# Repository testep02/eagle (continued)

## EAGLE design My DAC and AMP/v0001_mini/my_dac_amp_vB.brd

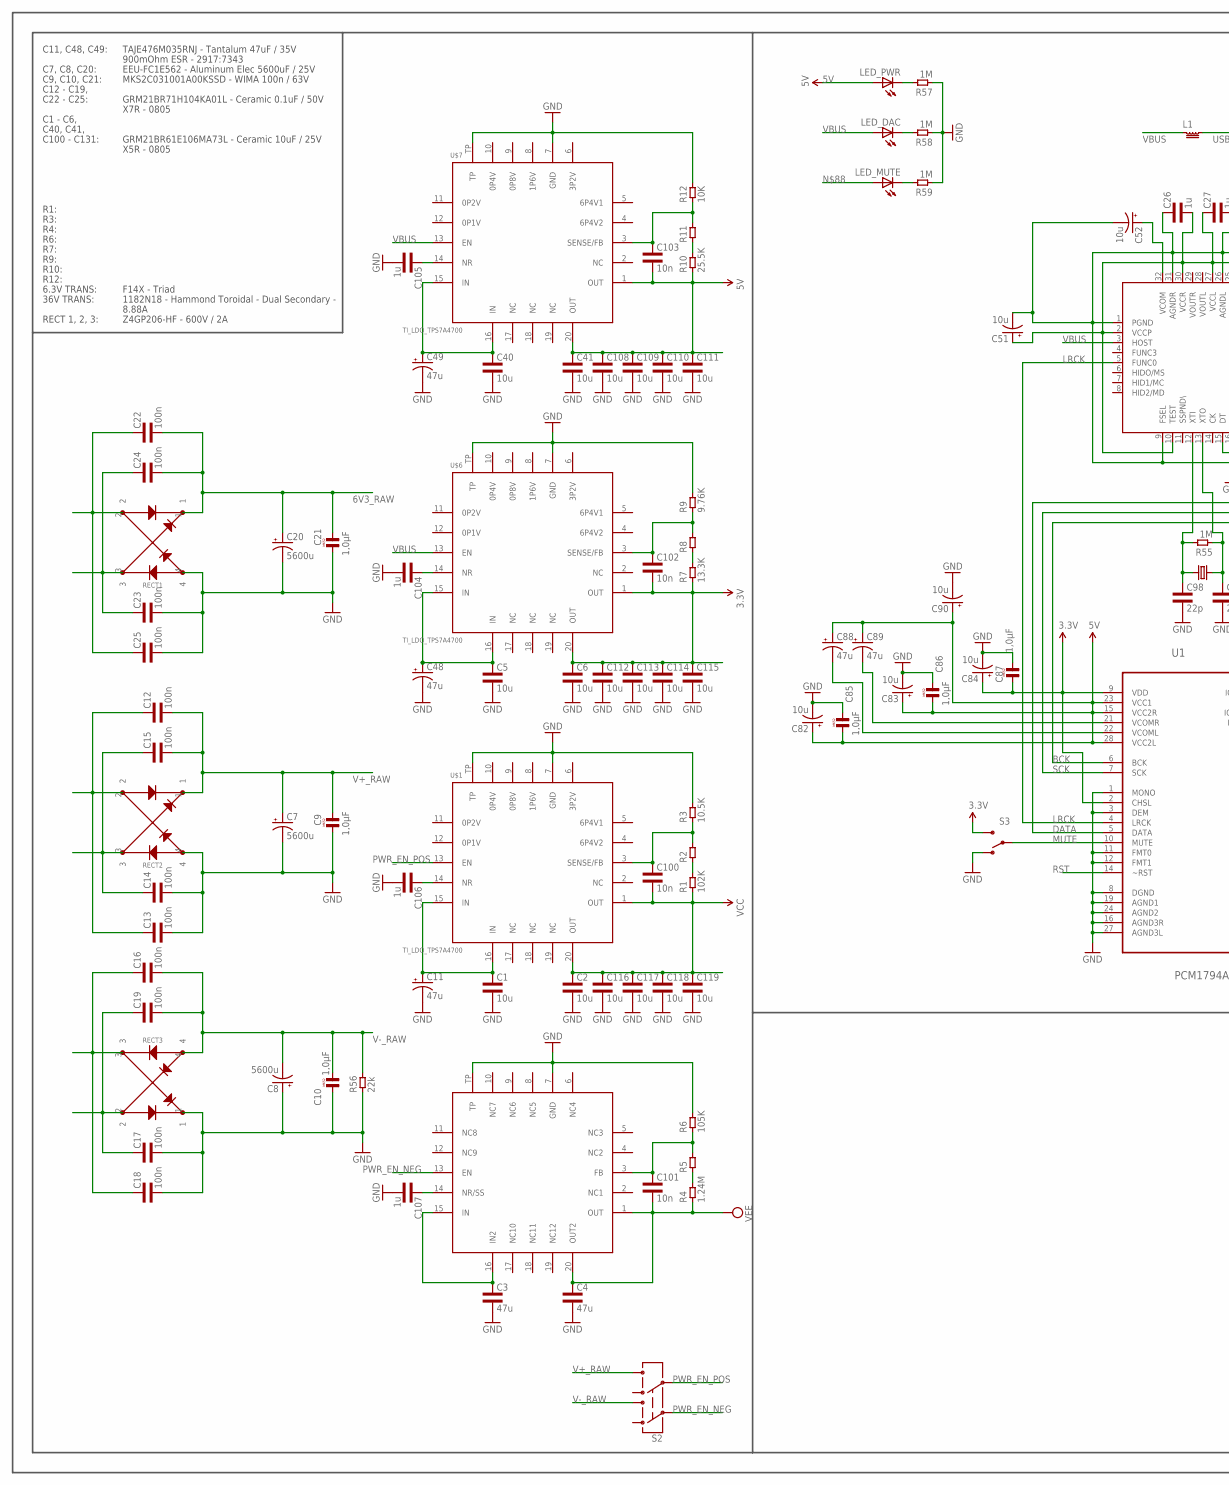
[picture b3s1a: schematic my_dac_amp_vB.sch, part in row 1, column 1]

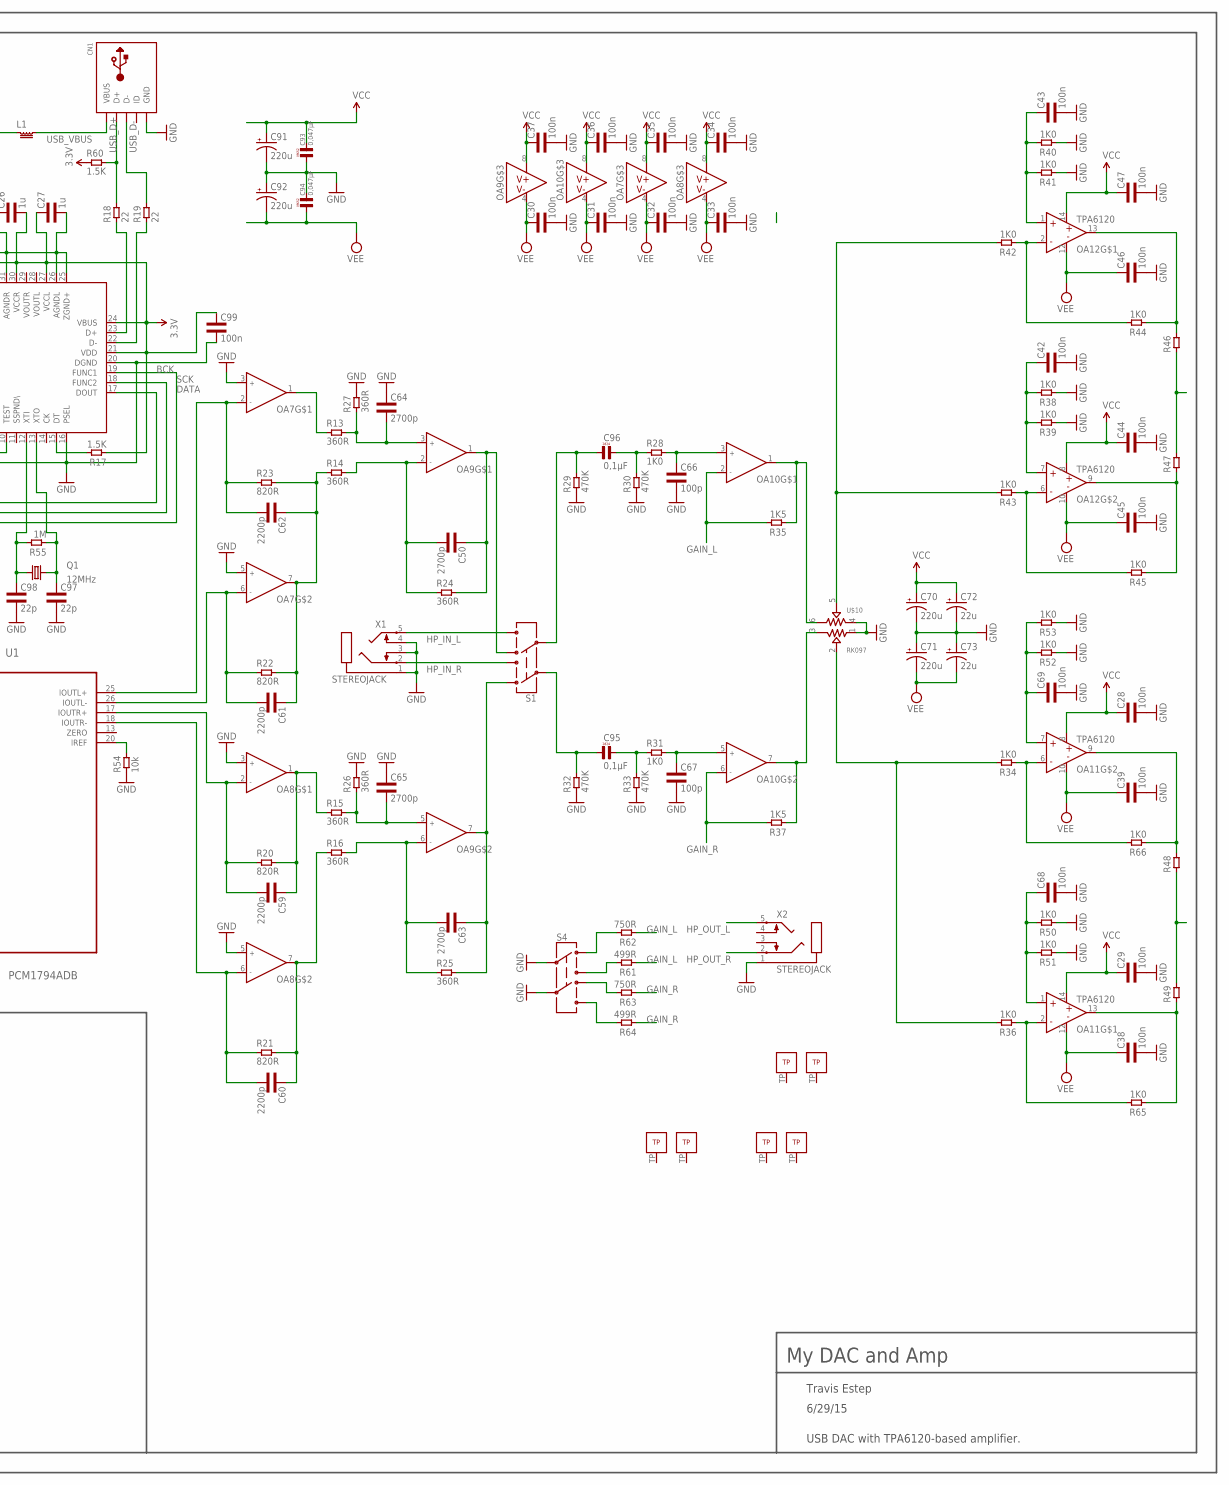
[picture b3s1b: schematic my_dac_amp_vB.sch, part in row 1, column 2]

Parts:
C1, C5, C40: 10u; 1206L3
C2, C6, C41, C108, C109, C110, C111, C112, C113, C114, C115, C116, C117, C118, C119: 10u; 0805L3
C3, C4: 47u; 1206L3
C7, C8, C20: 5600u; E7,5-16
C9, C10, C21, C85, C86, C87: 1,0µF; R5B5
C11, C48, C49: 47u; SMC_E
C12, C13, C14, C15, C16, C17, C18, C19, C22, C23, C24, C25: 100n; 0805L3
C26, C27, C104, C105, C106, C107: 1u; 0603L3
C28, C29, C30, C31, C32, C33, C34, C35, C36, C37, C38, C39, C42, C43, C44, C45, C46, C47, C68, C69, C99: 100n; 0603L3
C50, C63, C64, C65: 2700p; 0603L3
C51, C52, C82, C83, C84, C90: 10u; E3,5-8
C59, C60, C61, C62: 2200p; 0603L3
C66, C67: 100p; 0603L3
C70, C71, C91, C92: 220u; E5-13
C72, C73: 22u; E3,5-8
C88, C89: 47u; E5-10,5
C93, C94: 0,047µF; R5B2K5
C95, C96: 0,1µF; L7,2
C97, C98: 22p; 0603L3
C100, C101, C102, C103: 10n; 0603L3
CN1: USBMINIB; USB-MINIB
L1: SRP4020; 4440
LED_DAC: LED3MM
LED_MUTE: LED3MM
LED_PWR: LED3MM
OA7, OA8, OA9, OA10: OPA1612; S-PWSON-N8
OA11, OA12: TPA6120QFN; S-PVQFN-N14
Q1: 12MHz; SPARKFUN_HC49US
R1: 102K; 0603L3
R2, R5, R8, R11: RES0603L3; 0603L3
R3: 10.5K; 0603L3
R4: 1.24M; 0603L3
R6: 105K; 0603L3
R7: 13.3K; 0603L3
R9: 9.76K; 0603L3
R10: 25.5K; 0603L3
R12: 10K; 0603L3
R13, R14, R15, R16, R24, R25, R26, R27: 360R; 0603L3
R17, R60: 1.5K; 0603L3
R18, R19: 22; 0603L3
R20, R21, R22, R23: 820R; 0603L3
R28, R31, R34, R36, R38, R39, R40, R41, R42, R43, R44, R45, R50, R51, R52, R53, R65, R66: 1K0; 0603L3
R29, R30, R32, R33: 470K; 0603L3
R35, R37: 1K5; 0603L3
R46, R47, R48, R49: RES1206L3; 1206L3
R54: 10k; 0603L3
R55, R57, R58, R59: 1M; 0603L3
R56: 22k; 0805L3
R61, R64: 499R; 0603L3
R62, R63: 750R; 0603L3
RECT1, RECT2, RECT3: Z4GP206; ABS-4
S1, S2, S4: SWITCH-DPDTOS; OS
S3: SWITCH-SPDTKIT; SWITCH-SPDT_KIT
U1: PCM1794ADB; SOP65P780X200-28N
U$1, U$6, U$7: TI_LDO_TPS7A4700; TI_LDO_VQFN-20
U$2: TI_LDO_TPS7A3301RGWT; TI_LDO_VQFN-20
U$3: PCM2704C_PCM2707
U$10: RK097
X1, X2: STEREOJACK; STX3100

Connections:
3.3V: C6.1, C26.P$2 (2), C27.P$1 (1), C51.+, C84.+, C87.1, C99.P$1 (1), C102.P$2 (2), C112.1, C113.1, C114.1, C115.1, R7.P$1 (1), R17.P$1 (1), R60.P$1 (1), S3.3 (S), U1.2 (CHSL), U1.9 (VDD), U$3.2 (VCCP), U$3.10 (TEST), U$3.21 (VDD), U$3.24 (VBUS), U$3.27 (VCCL), U$3.30 (VCCR), U$6.1 (OUT), U$6.20 (OUT)
5V: C41.1, C82.+, C83.+, C85.1, C86.1, C88.+, C89.+, C90.+, C103.P$2 (2), C108.1, C109.1, C110.1, C111.1, LED_PWR.A, R10.P$1 (1), U1.15 (VCC2R), U1.23 (VCC1), U1.28 (VCC2L), U$7.1 (OUT), U$7.20 (OUT)
6V3_RAW: C5.1, C20.+, C21.2, C22.2, C24.2, C40.1, C48.+, C49.+, RECT1.1, U$6.15 (IN), U$6.16 (IN), U$7.15 (IN), U$7.16 (IN)
BCK: U1.6 (BCK), U$3.19 (FUNC1)
D+: R18.P$1 (1), U$3.23 (D+)
D-: R19.P$1 (1), U$3.22 (D-)
DATA: U1.5 (DATA), U$3.17 (DOUT)
GAIN_L: OA10.2 (INA-), R35.P$2 (2), R61.P$1 (1), R62.P$1 (1)
GAIN_R: OA10.6 (INB-), R37.P$2 (2), R63.P$1 (1), R64.P$1 (1)
GND: C1.2, C2.2, C3.2, C4.2, C5.2, C6.2, C7.-, C8.+, C9.1, C10.1, C11.-, C13.2, C14.2, C17.2, C18.2, C20.-, C21.1, C23.2, C25.2, C26.P$1 (1), C27.P$2 (2), C28.P$2 (2), C29.P$2 (2), C30.P$2 (2), C31.P$2 (2), C32.P$2 (2), C33.P$2 (2), C34.P$2 (2), C35.P$2 (2), C36.P$2 (2), C37.P$2 (2), C38.P$2 (2), C39.P$2 (2), C40.2, C41.2, C42.P$2 (2), C43.P$2 (2), C44.P$2 (2), C45.P$2 (2), C46.P$2 (2), C47.P$2 (2), C48.-, C49.-, C51.-, C52.-, C64.P$1 (1), C65.P$1 (1), C66.P$2 (2), C67.P$2 (2), C68.P$2 (2), C69.P$2 (2), C70.-, C71.+, C72.-, C73.+, C82.-, C83.-, C84.-, C85.2, C86.2, C87.2, C90.-, C91.-, C92.+, C93.1, C94.2, C97.P$2 (2), C98.P$2 (2), C99.P$2 (2), C104.P$2 (2), C105.P$2 (2), C106.P$2 (2), C107.P$2 (2), C108.2, C109.2, C110.2, C111.2, C112.2, C113.2, C114.2, C115.2, C116.2, C117.2, C118.2, C119.2, CN1.GND, OA7.3 (INA+), OA7.5 (INB+), OA8.3 (INA+), OA8.5 (INB+), R3.P$2 (2), R6.P$2 (2), R9.P$2 (2), R12.P$2 (2), R26.P$2 (2), R27.P$2 (2), R29.P$1 (1), R30.P$1 (1), R32.P$1 (1), R33.P$1 (1), R38.P$1 (1), R39.P$1 (1), R40.P$1 (1), R41.P$1 (1), R50.P$1 (1), R51.P$1 (1), R52.P$1 (1), R53.P$1 (1), R54.P$1 (1), R56.1, R57.P$1 (1), R58.P$1 (1), R59.P$1 (1), RECT1.4, RECT2.4, RECT3.1, S3.1 (O), S4.2, S4.5, U1.1 (MONO), U1.3 (DEM), U1.8 (DGND), U1.11 (FMT0), U1.12 (FMT1), U1.16 (AGND3R), U1.19 (AGND1), U1.24 (AGND2), U1.27 (AGND3L), U$1.7 (GND), U$1.TP, U$2.7 (GND), U$2.TP, U$3.1 (PGND), U$3.9 (FSEL), U$3.16 (PSEL), U$3.20 (DGND), U$3.25 (ZGND+), U$3.26 (AGNDL), U$3.31 (AGNDR), U$6.7 (GND), U$6.TP, U$7.7 (GND), U$7.TP, U$10.1, U$10.4, X1.1, X1.3, X1.4, X2.1
HP_IN_L: S1.6, X1.5
HP_IN_R: S1.3, X1.2
HP_OUT_L: R46.1, R47.2, X2.5
HP_OUT_R: R48.1, R49.2, X2.2
LRCK: U1.4 (LRCK), U$3.5 (FUNC0)
MUTE: S3.2, U1.10 (MUTE)
unnamed: R10.P$2 (2), R11.P$1 (1)
unnamed: R1.P$2 (2), R2.P$1 (1)
unnamed: C100.P$1 (1), R2.P$2 (2), R3.P$1 (1), U$1.3 (SENSE/FB)
unnamed: LED_PWR.K (C), R57.P$2 (2)
unnamed: LED_DAC.K (C), R58.P$2 (2)
unnamed: C103.P$1 (1), R11.P$2 (2), R12.P$1 (1), U$7.3 (SENSE/FB)
unnamed: R4.P$2 (2), R5.P$1 (1)
unnamed: C101.P$1 (1), R5.P$2 (2), R6.P$1 (1), U$2.3 (FB)
unnamed: C62.P$2 (2), OA7.2 (INA-), R23.P$1 (1), U1.25 (IOUTL+)
unnamed: C42.P$1 (1), OA12.7 (IN+), R38.P$2 (2), R39.P$2 (2)
unnamed: C43.P$1 (1), OA12.1 (IN+), R40.P$2 (2), R41.P$2 (2)
unnamed: C12.1, C13.1, RECT2.2
unnamed: C14.1, C15.1, RECT2.3
unnamed: OA7.1 (OUTA), R13.P$1 (1)
unnamed: C61.P$1 (1), C62.P$1 (1), OA7.7 (OUTB), R14.P$1 (1), R22.P$2 (2), R23.P$2 (2)
unnamed: C50.P$1 (1), OA9.1 (OUTA), R24.P$2 (2), S1.4
unnamed: R7.P$2 (2), R8.P$1 (1)
unnamed: C102.P$1 (1), R8.P$2 (2), R9.P$1 (1), U$6.3 (SENSE/FB)
unnamed: R62.P$2 (2), S4.1
unnamed: C63.P$1 (1), OA9.7 (OUTB), R25.P$2 (2), S1.1
unnamed: C59.P$2 (2), OA8.2 (INA-), R20.P$1 (1), U1.17 (IOUTR+)
unnamed: C60.P$2 (2), OA8.6 (INB-), R21.P$1 (1), U1.18 (IOUTR-)
unnamed: C23.1, C24.1, RECT1.3
unnamed: C22.1, C25.1, RECT1.2
unnamed: R61.P$2 (2), S4.3
unnamed: C64.P$2 (2), OA9.3 (INA+), R13.P$2 (2), R27.P$1 (1)
unnamed: OA12.2 (IN-), R42.P$1 (1), R44.P$2 (2)
unnamed: OA12.6 (IN-), R43.P$1 (1), R45.P$2 (2)
unnamed: OA10.7 (OUTB), R37.P$1 (1), U$10.3
unnamed: C59.P$1 (1), OA8.1 (OUTA), R15.P$1 (1), R20.P$2 (2)
unnamed: C61.P$2 (2), OA7.6 (INB-), R22.P$1 (1), U1.26 (IOUTL-)
unnamed: C52.+, U$3.32 (VCOM)
unnamed: R17.P$2 (2), U$3.15 (DT)
unnamed: C63.P$2 (2), OA9.6 (INB-), R16.P$2 (2), R25.P$1 (1)
unnamed: C60.P$1 (1), OA8.7 (OUTB), R16.P$1 (1), R21.P$2 (2)
unnamed: OA11.13 (OUT), R49.1, R65.P$1 (1)
unnamed: OA11.2 (IN-), R36.P$1 (1), R65.P$2 (2)
unnamed: OA11.9 (OUT), R48.2, R66.P$1 (1)
unnamed: OA11.6 (IN-), R34.P$1 (1), R66.P$2 (2)
unnamed: R34.P$2 (2), R36.P$2 (2), U$10.2
unnamed: OA12.13 (OUT), R44.P$1 (1), R46.2
unnamed: OA12.9 (OUT), R45.P$1 (1), R47.1
unnamed: C96.P$2 (2), R28.P$1 (1), R30.P$2 (2)
unnamed: C66.P$1 (1), OA10.3 (INA+), R28.P$2 (2)
unnamed: C65.P$2 (2), OA9.5 (INB+), R15.P$2 (2), R26.P$1 (1)
unnamed: C107.P$1 (1), U$2.14 (NR/SS)
unnamed: C106.P$1 (1), U$1.14 (NR)
unnamed: C50.P$2 (2), OA9.2 (INA-), R14.P$2 (2), R24.P$1 (1)
unnamed: C104.P$1 (1), U$6.14 (NR)
unnamed: C105.P$1 (1), U$7.14 (NR)
unnamed: C95.P$2 (2), R31.P$1 (1), R33.P$2 (2)
unnamed: C67.P$1 (1), OA10.5 (INB+), R31.P$2 (2)
unnamed: C68.P$1 (1), OA11.1 (IN+), R50.P$2 (2), R51.P$2 (2)
unnamed: C96.P$1 (1), R29.P$2 (2), S1.5
unnamed: C95.P$1 (1), R32.P$2 (2), S1.2
unnamed: C16.1, C18.1, RECT3.3
unnamed: C69.P$1 (1), OA11.7 (IN+), R52.P$2 (2), R53.P$2 (2)
unnamed: R42.P$2 (2), R43.P$2 (2), U$10.5
unnamed: C17.1, C19.1, RECT3.2
unnamed: C89.-, U1.21 (VCOMR)
unnamed: C88.-, U1.22 (VCOML)
unnamed: C98.P$1 (1), Q1.1, R55.P$2 (2), U$3.12 (XTI)
unnamed: OA10.1 (OUTA), R35.P$1 (1), U$10.6
unnamed: C97.P$1 (1), Q1.2, R55.P$1 (1), U$3.13 (XTO)
unnamed: LED_MUTE.K (C), R59.P$2 (2)
unnamed: R54.P$2 (2), U1.20 (IREF)
unnamed: R63.P$2 (2), S4.4
unnamed: R64.P$2 (2), S4.6
PWR_EN_NEG: S2.2, U$2.13 (EN)
PWR_EN_POS: S2.5, U$1.13 (EN)
RST: U1.14 (~RST)
SCK: U1.7 (SCK), U$3.18 (FUNC2)
USB_D+: CN1.D+, R18.P$2 (2), R60.P$2 (2)
USB_D-: CN1.D-, R19.P$2 (2)
USB_VBUS: CN1.VBUS, L1.2
V+_RAW: C1.1, C7.+, C9.2, C11.+, C12.2, C15.2, RECT2.1, S2.6, U$1.15 (IN), U$1.16 (IN)
V-_RAW: C3.1, C8.-, C10.2, C16.2, C19.2, R56.2, RECT3.4, S2.3, U$2.15 (IN), U$2.16 (IN2)
VBUS: L1.1, LED_DAC.A, U$3.3 (HOST), U$6.13 (EN), U$7.13 (EN)
VCC: C2.1, C28.P$1 (1), C29.P$1 (1), C34.P$1 (1), C35.P$1 (1), C36.P$1 (1), C37.P$1 (1), C44.P$1 (1), C47.P$1 (1), C70.+, C72.+, C91.+, C93.2, C100.P$2 (2), C116.1, C117.1, C118.1, C119.1, OA7.8 (V+), OA8.8 (V+), OA9.8 (V+), OA10.8 (V+), OA11.8 (V+), OA11.14 (V+), OA12.8 (V+), OA12.14 (V+), R1.P$1 (1), U$1.1 (OUT), U$1.20 (OUT)
VEE: C4.1, C30.P$1 (1), C31.P$1 (1), C32.P$1 (1), C33.P$1 (1), C38.P$1 (1), C39.P$1 (1), C45.P$1 (1), C46.P$1 (1), C71.-, C73.-, C92.-, C94.1, C101.P$2 (2), OA7.4 (V-), OA8.4 (V-), OA9.4 (V-), OA10.4 (V-), OA11.10 (V-), OA11.12 (V-), OA12.10 (V-), OA12.12 (V-), R4.P$1 (1), U$2.1 (OUT), U$2.20 (OUT2)

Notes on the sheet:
C11, C48, C49:
TAJE476M035RNJ - Tantalum 47uF / 35V
900mOhm ESR - 2917:7343
C7, C8, C20:
EEU-FC1E562 - Aluminum Elec 5600uF / 25V
RECT 1, 2, 3:
Z4GP206-HF - 600V / 2A
C9, C10, C21:
MKS2C031001A00KSSD - WIMA 100n / 63V
6.3V TRANS:
F14X - Triad
36V TRANS:
1182N18 - Hammond Toroidal - Dual Secondary -
8.88A
GRM21BR71H104KA01L - Ceramic 0.1uF / 50V
X7R - 0805
R1:
R3:
R4:
R6:
R7:
R9:
R10:
R12:
GRM21BR61E106MA73L - Ceramic 10uF / 25V
X5R - 0805
C12 - C19,
C22 - C25:
C1 - C6,
C40, C41,
C100 - C131:
My DAC and Amp
Travis Estep
6/29/15
USB DAC with TPA6120-based amplifier.

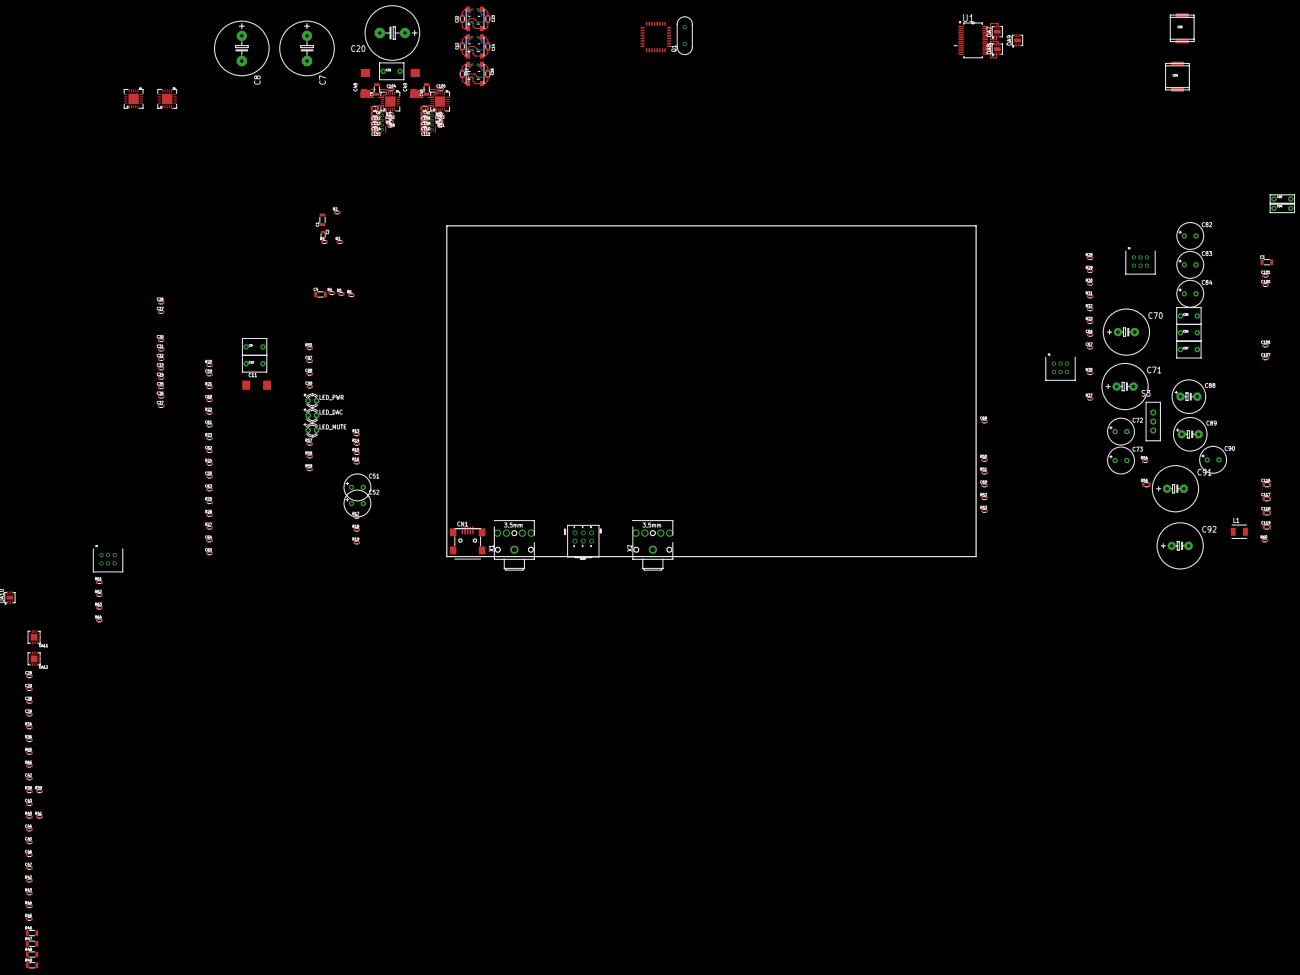
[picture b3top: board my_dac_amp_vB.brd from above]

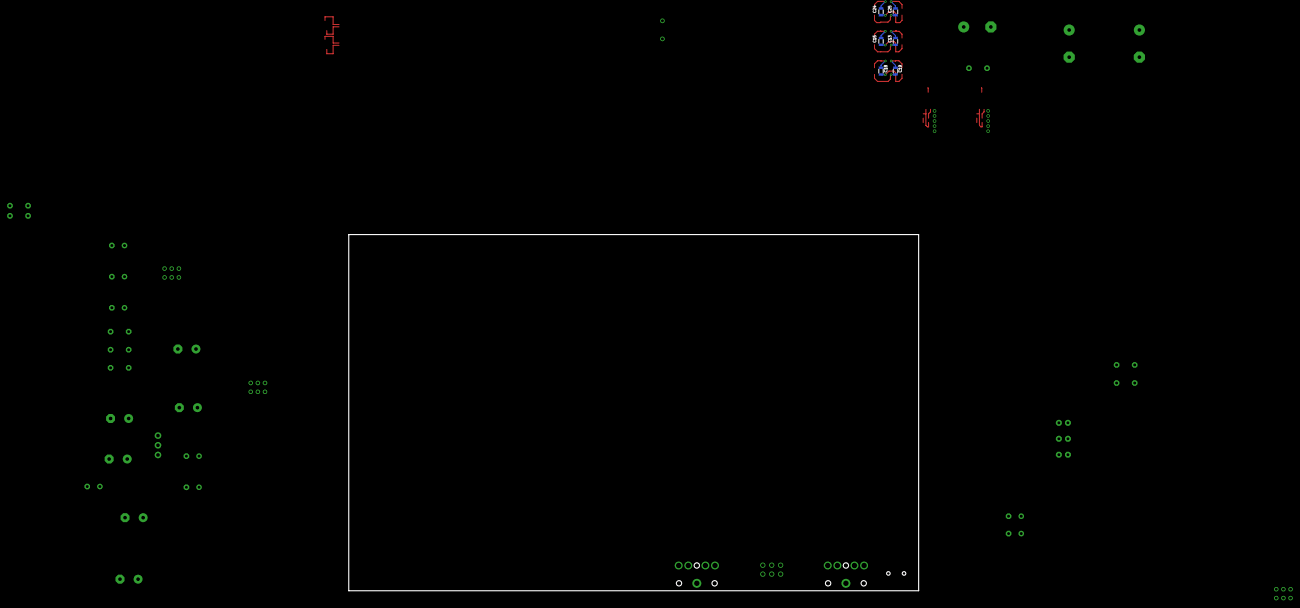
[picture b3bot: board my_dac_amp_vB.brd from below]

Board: 2 copper layers, 199 parts (6 on the bottom side), 95 nets.

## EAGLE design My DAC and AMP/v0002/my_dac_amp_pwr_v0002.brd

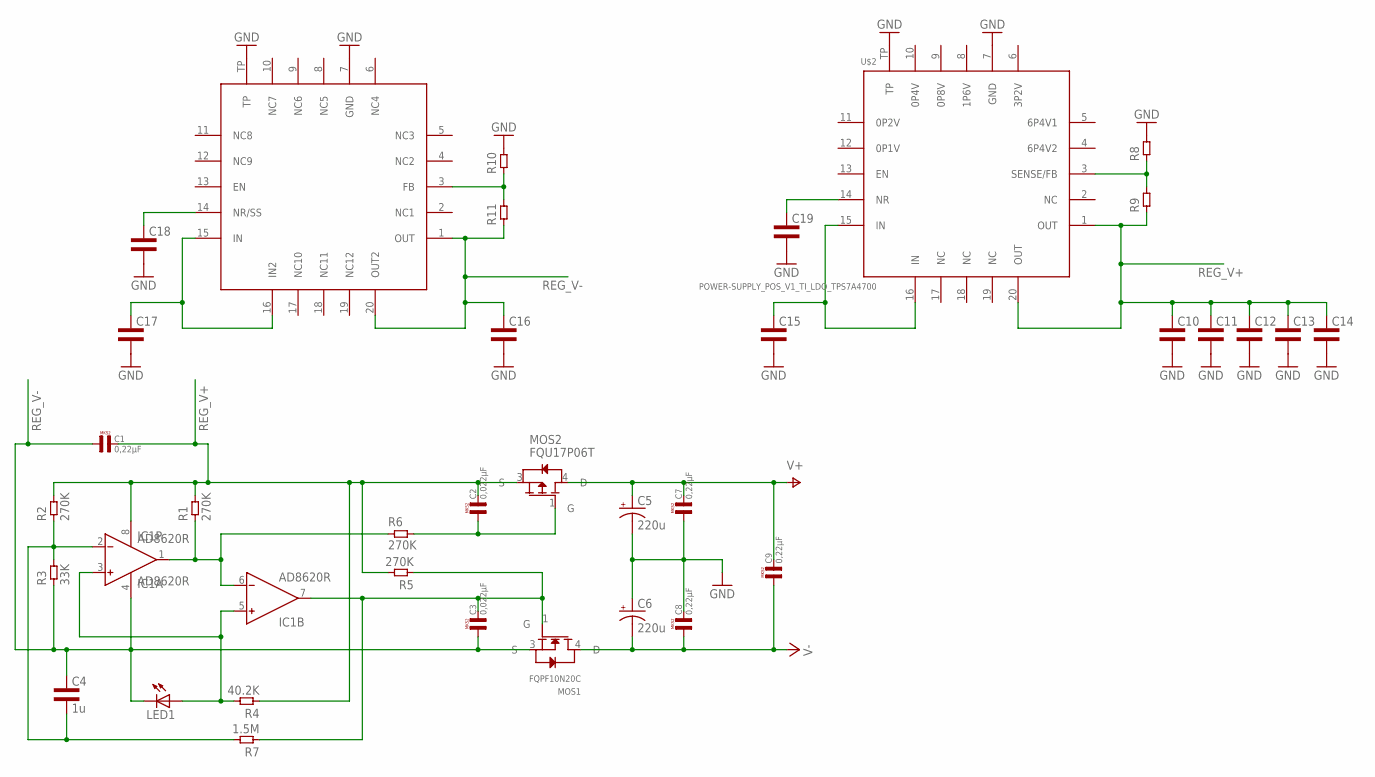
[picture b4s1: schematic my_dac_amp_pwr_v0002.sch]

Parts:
C1, C7, C8, C9: 0,22µF; R5B3
C2, C3: 0,022µF; R5B2K5
C4: 1u; 0805L3
C5, C6: 220u; E5-10,5
C10, C11, C12, C13, C14, C15, C16, C17: CAP0805L3; 0805L3
C18, C19: CAP0603L3; 0603L3
IC1: AD8620R; SO8
LED1: LED3MM
MOS1: FQPF10N20C; DPAK-3
MOS2: FQU17P06T; DPAK-3
R1, R2, R5, R6: 270K; 0805L3
R3: 33K; 0805L3
R4: 40.2K; 0805L3
R7: 1.5M; 0805L3
R8, R9, R10, R11: RES0603L3; 0603L3
U$1: POWER-SUPPLY_POS_V1_TI_LDO_TPS7A3301RGWT; POWER-SUPPLY_POS_V1_TI_LDO_VQFN-20
U$2: POWER-SUPPLY_POS_V1_TI_LDO_TPS7A4700; POWER-SUPPLY_POS_V1_TI_LDO_VQFN-20

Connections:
GND: C5.-, C6.+, C7.1, C8.2, C10.2, C11.2, C12.2, C13.2, C14.2, C15.2, C16.2, C17.2, C18.P$2 (2), C19.P$2 (2), R8.P$2 (2), R10.P$2 (2), U$1.7 (GND), U$1.TP, U$2.7 (GND), U$2.TP
unnamed: IC1.3 (IN+), IC1.5 (IN+), LED1.A, R4.2
unnamed: C4.2, IC1.2 (IN-), R2.1, R3.2, R7.2
unnamed: IC1.1 (OUT), IC1.6 (IN-), R1.1, R6.1
unnamed: C17.1, U$1.15 (IN), U$1.16 (IN2)
unnamed: C2.1, MOS2.1 (G), R6.2
unnamed: C15.1, U$2.15 (IN), U$2.16 (IN)
unnamed: C3.2, IC1.7 (OUT), MOS1.1 (G), R5.1, R7.1
unnamed: R10.P$1 (1), R11.P$2 (2), U$1.3 (FB)
unnamed: R8.P$1 (1), R9.P$2 (2), U$2.3 (SENSE/FB)
unnamed: C18.P$1 (1), U$1.14 (NR/SS)
unnamed: C19.P$1 (1), U$2.14 (NR)
REG_V+: C1.2, C2.2, C10.1, C11.1, C12.1, C13.1, C14.1, IC1.8 (V+), MOS2.3 (S), R1.2, R2.2, R4.1, R5.2, R9.P$1 (1), U$2.1 (OUT), U$2.20 (OUT)
REG_V-: C1.1, C3.1, C4.1, C16.1, IC1.4 (V-), LED1.K (C), MOS1.3 (S), R3.1, R11.P$1 (1), U$1.1 (OUT), U$1.20 (OUT2)
V+: C5.+, C7.2, C9.2, MOS2.4 (D)
V-: C6.-, C8.1, C9.1, MOS1.4 (D)

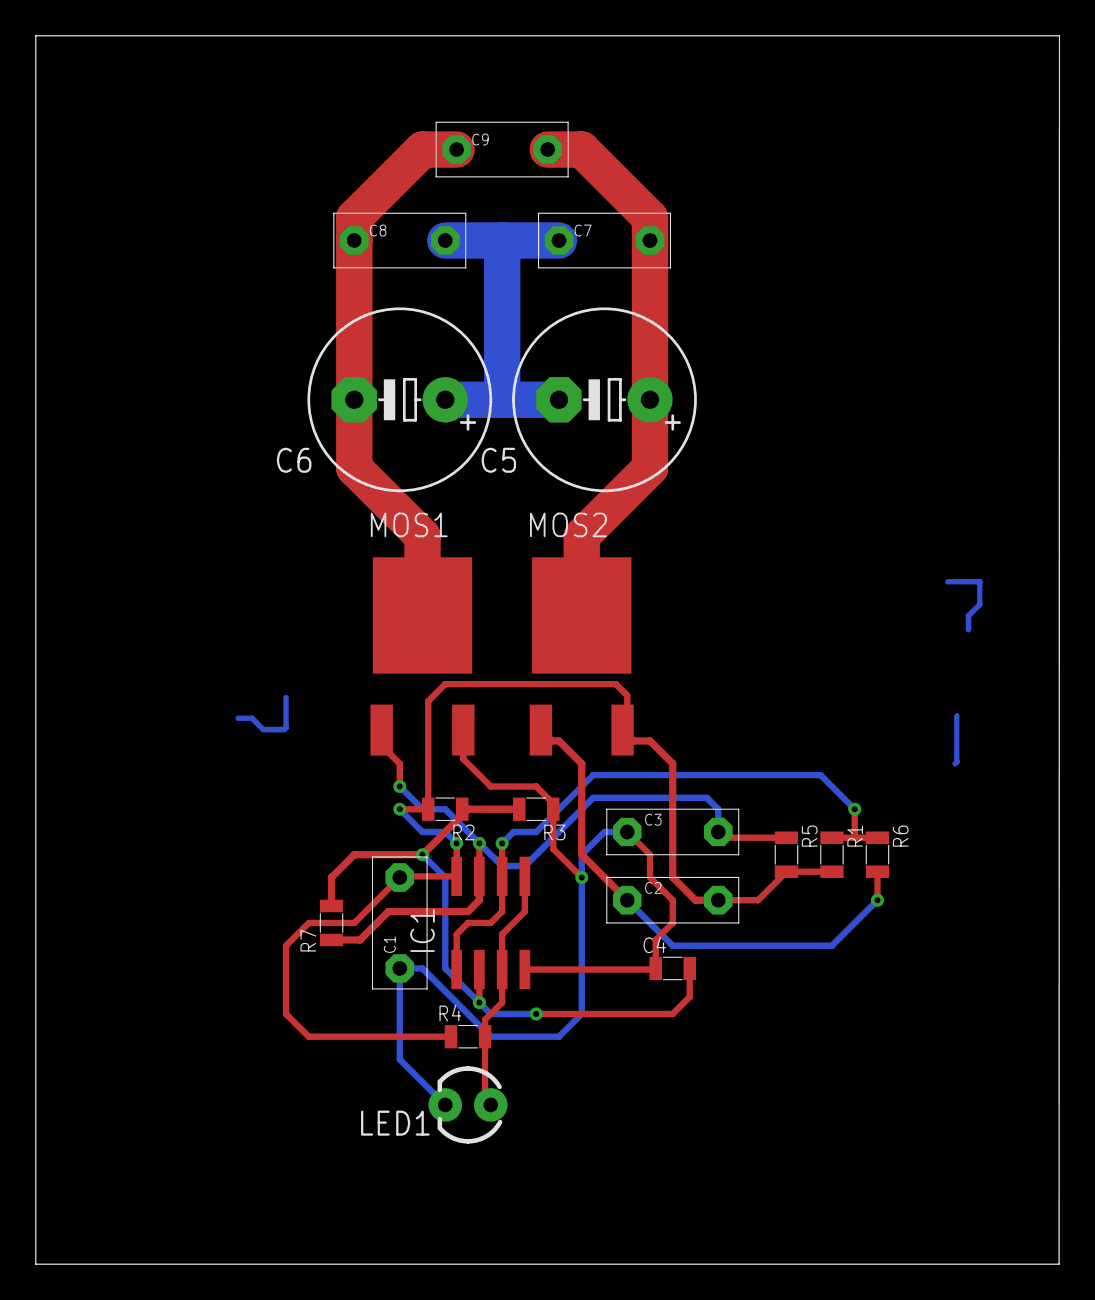
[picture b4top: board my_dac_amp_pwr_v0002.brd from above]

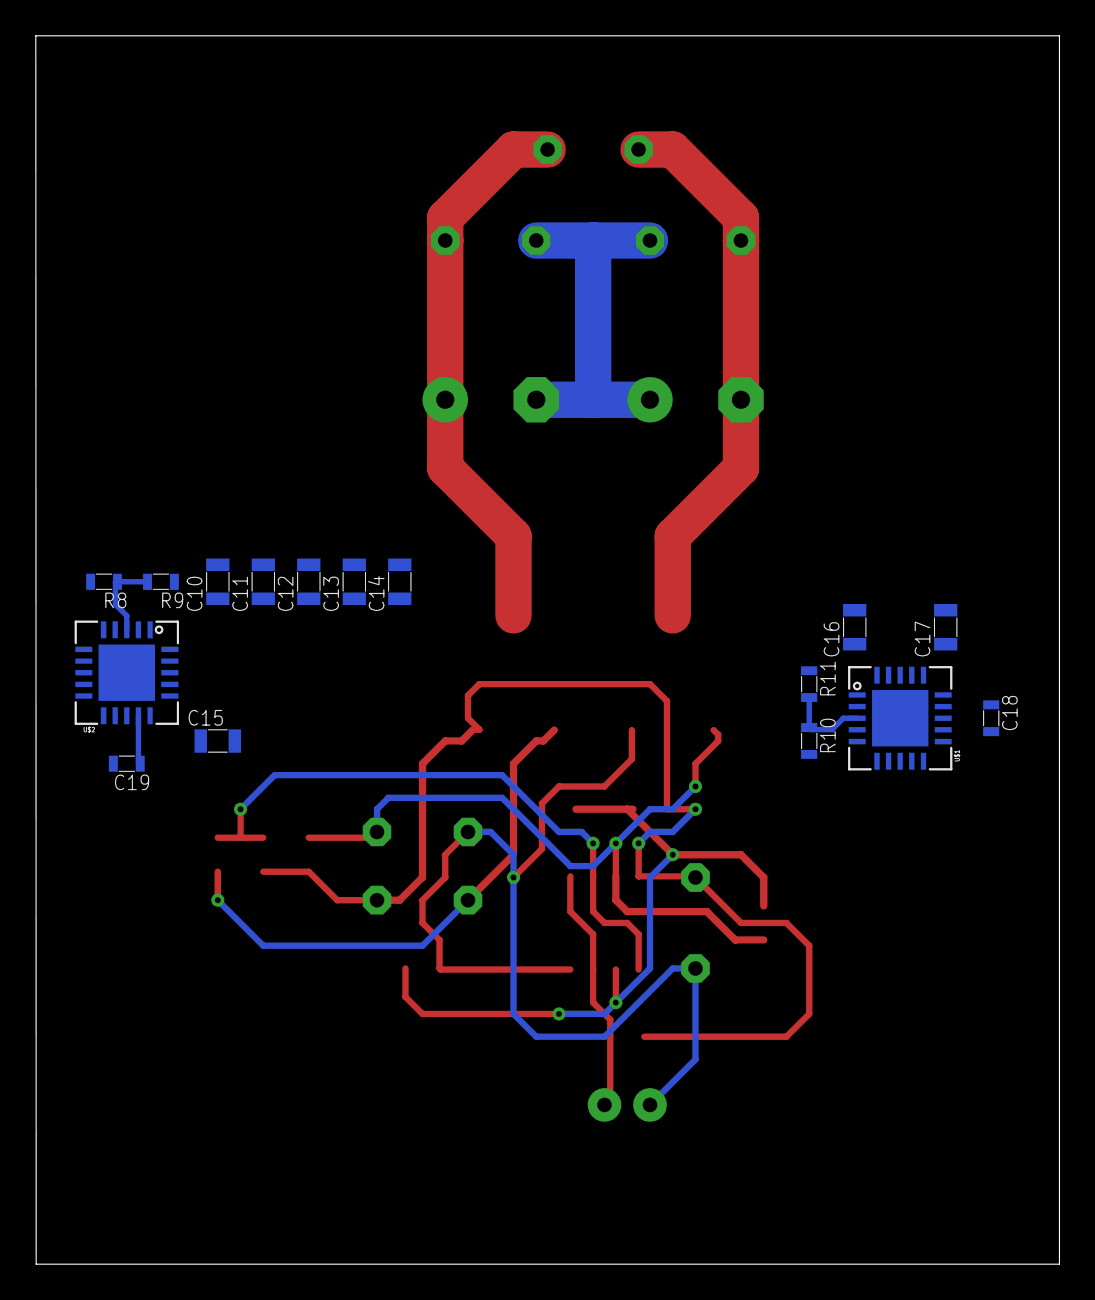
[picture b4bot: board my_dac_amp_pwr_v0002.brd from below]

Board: 2 copper layers, 57.1 x 68.6 mm, 36 parts (16 on the bottom side), 16 nets.

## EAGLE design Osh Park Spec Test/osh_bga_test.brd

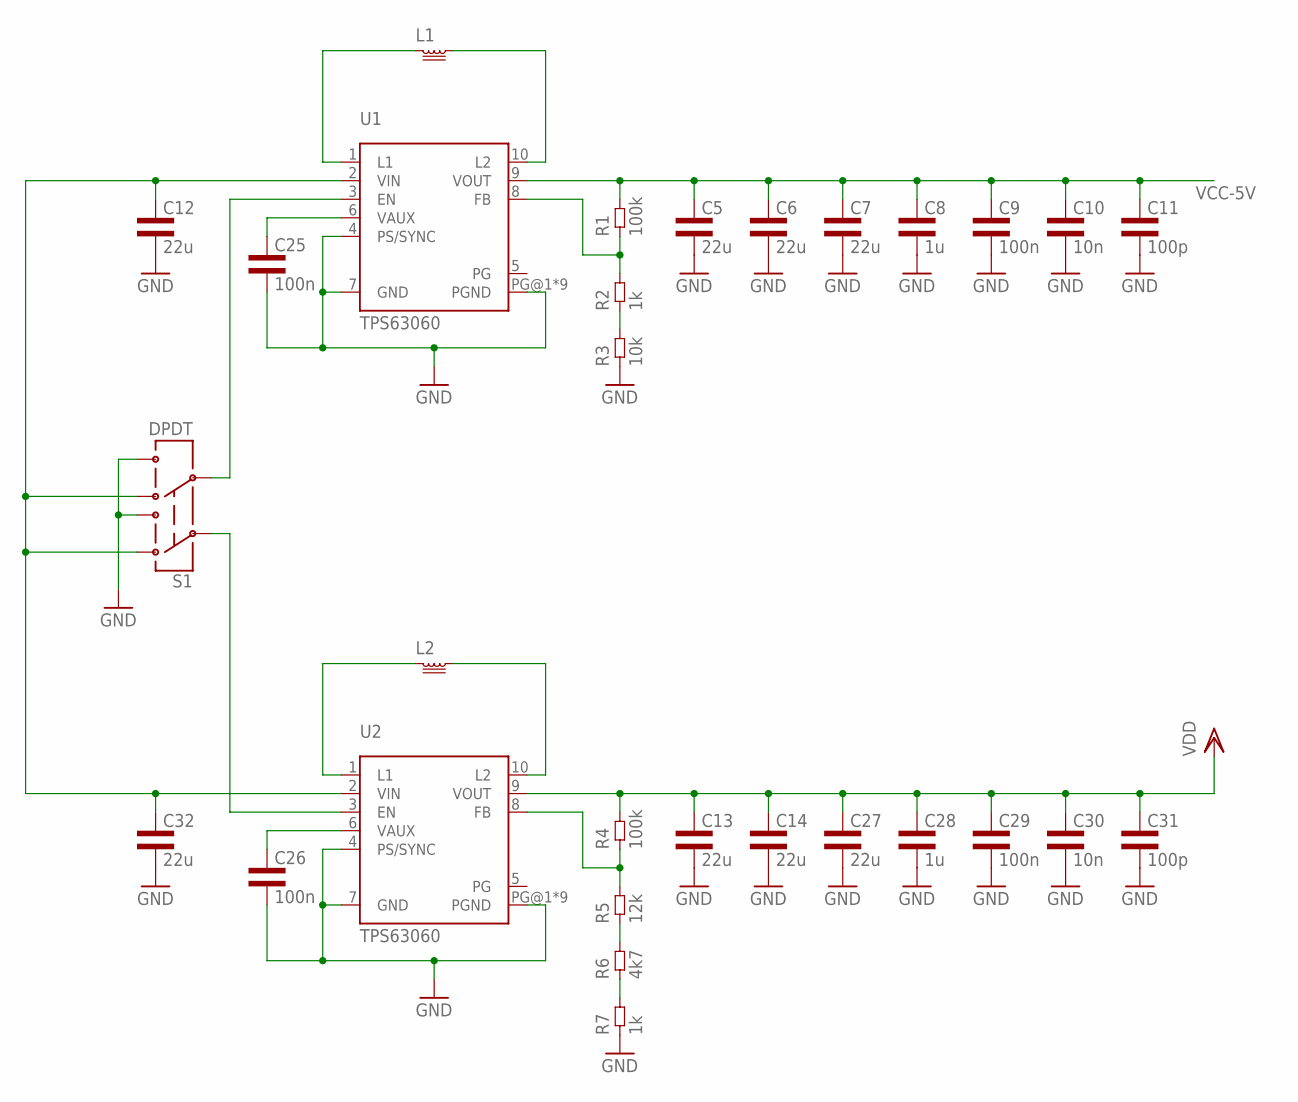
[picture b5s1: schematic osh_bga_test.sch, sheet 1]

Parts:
C5, C6, C7, C12, C13, C14, C27, C32: 22u; 1206L3
C8, C28: 1u; 0805L3
C9, C25, C26, C29: 100n; 0603L3
C10, C30: 10n; 0603L3
C11, C31: 100p; 0603L3
L1, L2: INDUCTORSRP4020; SRP4020
R1, R4: 100k; 0603L3
R2, R7: 1k; 0603L3
R3: 10k; 0603L3
R5: 12k; 0603L3
R6: 4k7; 0603L3
S1: DPDT; AYZ0202
U1, U2: TPS63060; S-PWSON-N10

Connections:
GND: C5.2, C6.2, C7.2, C8.2, C9.P$2 (2), C10.P$2 (2), C11.P$2 (2), C12.2, C13.2, C14.2, C25.P$2 (2), C26.P$2 (2), C27.2, C28.2, C29.P$2 (2), C30.P$2 (2), C31.P$2 (2), C32.2, R3.P$1 (1), R7.P$1 (1), S1.3, S1.6, U1.4 (PS/SYNC), U1.7 (GND), U1.PG@1 (PGND), U1.PG@2 (PGND), U1.PG@3 (PGND), U1.PG@4 (PGND), U1.PG@5 (PGND), U1.PG@6 (PGND), U1.PG@7 (PGND), U1.PG@8 (PGND), U1.PG@9 (PGND), U2.4 (PS/SYNC), U2.7 (GND), U2.PG@1 (PGND), U2.PG@2 (PGND), U2.PG@3 (PGND), U2.PG@4 (PGND), U2.PG@5 (PGND), U2.PG@6 (PGND), U2.PG@7 (PGND), U2.PG@8 (PGND), U2.PG@9 (PGND); also elsewhere on the board
unnamed: L1.1, U1.1 (L1)
unnamed: L1.2, U1.10 (L2)
unnamed: R1.P$1 (1), R2.P$2 (2), U1.8 (FB)
unnamed: S1.5, U1.3 (EN)
unnamed: L2.1, U2.1 (L1)
unnamed: L2.2, U2.10 (L2)
unnamed: S1.2, U2.3 (EN)
unnamed: R2.P$1 (1), R3.P$2 (2)
unnamed: R4.P$1 (1), R5.P$2 (2), U2.8 (FB)
unnamed: R5.P$1 (1), R6.P$2 (2)
unnamed: R6.P$1 (1), R7.P$2 (2)
unnamed: C25.P$1 (1), U1.6 (VAUX)
unnamed: C26.P$1 (1), U2.6 (VAUX)
VBAT: C12.1, C32.1, S1.1, S1.4, U1.2 (VIN), U2.2 (VIN)
VCC-5V: C5.1, C6.1, C7.1, C8.1, C9.P$1 (1), C10.P$1 (1), C11.P$1 (1), R1.P$2 (2), U1.9 (VOUT)
VDD: C13.1, C14.1, C27.1, C28.1, C29.P$1 (1), C30.P$1 (1), C31.P$1 (1), R4.P$2 (2), U2.9 (VOUT); also elsewhere on the board

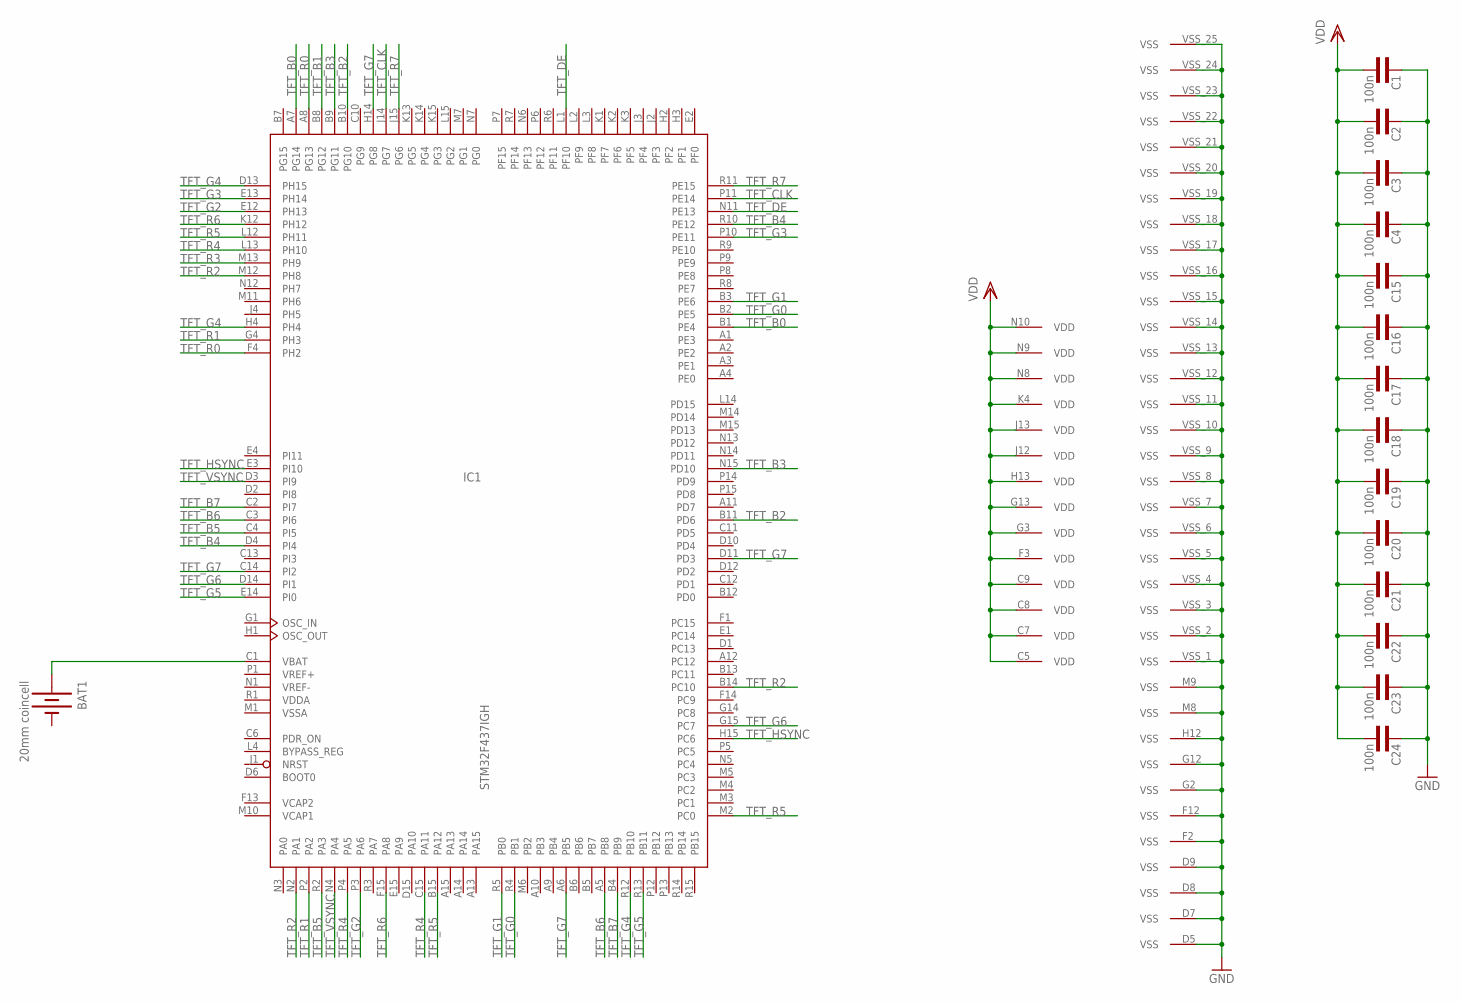
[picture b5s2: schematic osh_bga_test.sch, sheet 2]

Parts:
BAT1: 20mm coincell; BATTCON_20MM_4LEGS
C1, C2, C3, C4, C15, C16, C17, C18, C19, C20, C21, C22, C23, C24: 100n; 0402L3
IC1: STM32F437IGH; UFBGA176+25

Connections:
-: BAT1.2 (-)
GND: C1.P$1 (1), C2.P$1 (1), C3.P$1 (1), C4.P$1 (1), C15.P$1 (1), C16.P$1 (1), C17.P$1 (1), C18.P$1 (1), C19.P$1 (1), C20.P$1 (1), C21.P$1 (1), C22.P$1 (1), C23.P$1 (1), C24.P$1 (1), IC1.D5 (VSS), IC1.D7 (VSS), IC1.D8 (VSS), IC1.D9 (VSS), IC1.F2 (VSS), IC1.F12 (VSS), IC1.G2 (VSS), IC1.G12 (VSS), IC1.H12 (VSS), IC1.M8 (VSS), IC1.M9 (VSS), IC1.M10 (VCAP1), IC1.VSS_1 (VSS), IC1.VSS_2 (VSS), IC1.VSS_3 (VSS), IC1.VSS_4 (VSS), IC1.VSS_5 (VSS), IC1.VSS_6 (VSS), IC1.VSS_7 (VSS), IC1.VSS_8 (VSS), IC1.VSS_9 (VSS), IC1.VSS_10 (VSS), IC1.VSS_11 (VSS), IC1.VSS_12 (VSS), IC1.VSS_13 (VSS), IC1.VSS_14 (VSS), IC1.VSS_15 (VSS), IC1.VSS_16 (VSS), IC1.VSS_17 (VSS), IC1.VSS_18 (VSS), IC1.VSS_19 (VSS), IC1.VSS_20 (VSS), IC1.VSS_21 (VSS), IC1.VSS_22 (VSS), IC1.VSS_23 (VSS), IC1.VSS_24 (VSS), IC1.VSS_25 (VSS); also elsewhere on the board
unnamed: BAT1.1 (+), IC1.C1 (VBAT)
TFT_B0: IC1.A7 (PG14), IC1.B1 (PE4); also elsewhere on the board
TFT_B1: IC1.B8 (PG12); also elsewhere on the board
TFT_B2: IC1.B10 (PG10), IC1.B11 (PD6); also elsewhere on the board
TFT_B3: IC1.B9 (PG11), IC1.N15 (PD10); also elsewhere on the board
TFT_B4: IC1.D4 (PI4), IC1.R10 (PE12); also elsewhere on the board
TFT_B5: IC1.C4 (PI5), IC1.R2 (PA3); also elsewhere on the board
TFT_B6: IC1.A5 (PB8), IC1.C3 (PI6); also elsewhere on the board
TFT_B7: IC1.B4 (PB9), IC1.C2 (PI7); also elsewhere on the board
TFT_CLK: IC1.J14 (PG7), IC1.P11 (PE14); also elsewhere on the board
TFT_DE: IC1.L1 (PF10), IC1.N11 (PE13); also elsewhere on the board
TFT_G0: IC1.B2 (PE5), IC1.R4 (PB1); also elsewhere on the board
TFT_G1: IC1.B3 (PE6), IC1.R5 (PB0); also elsewhere on the board
TFT_G2: IC1.E12 (PH13), IC1.P3 (PA6); also elsewhere on the board
TFT_G3: IC1.E13 (PH14), IC1.P10 (PE11); also elsewhere on the board
TFT_G4: IC1.D13 (PH15), IC1.H4, IC1.R12 (PB10); also elsewhere on the board
TFT_G5: IC1.E14 (PI0), IC1.R13 (PB11); also elsewhere on the board
TFT_G6: IC1.D14 (PI1), IC1.G15 (PC7); also elsewhere on the board
TFT_G7: IC1.A6 (PB5), IC1.C14 (PI2), IC1.D11 (PD3), IC1.H14 (PG8); also elsewhere on the board
TFT_HSYNC: IC1.E3 (PI10), IC1.H15 (PC6); also elsewhere on the board
TFT_R0: IC1.A8 (PG13), IC1.F4 (PH2); also elsewhere on the board
TFT_R1: IC1.G4 (PH3), IC1.P2 (PA2); also elsewhere on the board
TFT_R2: IC1.B14 (PC10), IC1.M12 (PH8), IC1.N2 (PA1); also elsewhere on the board
TFT_R3: IC1.M13 (PH9); also elsewhere on the board
TFT_R4: IC1.C15 (PA11), IC1.L13 (PH10), IC1.P4 (PA5); also elsewhere on the board
TFT_R5: IC1.B15 (PA12), IC1.L12 (PH11), IC1.M2 (PC0); also elsewhere on the board
TFT_R6: IC1.F15 (PA8), IC1.K12 (PH12); also elsewhere on the board
TFT_R7: IC1.J15 (PG6), IC1.R11 (PE15); also elsewhere on the board
TFT_VSYNC: IC1.D3 (PI9), IC1.N4 (PA4); also elsewhere on the board
VCAP2: IC1.F13 (VCAP2)
VDD: C1.P$2 (2), C2.P$2 (2), C3.P$2 (2), C4.P$2 (2), C15.P$2 (2), C16.P$2 (2), C17.P$2 (2), C18.P$2 (2), C19.P$2 (2), C20.P$2 (2), C21.P$2 (2), C22.P$2 (2), C23.P$2 (2), C24.P$2 (2), IC1.C5 (VDD), IC1.C7 (VDD), IC1.C8 (VDD), IC1.C9 (VDD), IC1.F3 (VDD), IC1.G3 (VDD), IC1.G13 (VDD), IC1.H13 (VDD), IC1.J12 (VDD), IC1.J13 (VDD), IC1.K4 (VDD), IC1.N8 (VDD), IC1.N9 (VDD), IC1.N10 (VDD); also elsewhere on the board
VDDA: IC1.R1 (VDDA)
VREF+: IC1.P1 (VREF+)
VREF-: IC1.N1 (VREF-)
VSSA: IC1.M1 (VSSA)
